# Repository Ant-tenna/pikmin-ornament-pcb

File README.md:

# Pikmin ornament

## What it is?
Is a christmas tree ornament PCB designed with the shape of a pikmin. The lights blink every few seconds being driven by a 555 timer
and powered by a 3v coin cell battery. I was inspired by those images of the yellow pikmin with the christmas leds! lovethem

## BOM

| Component | Value | Quantity |
|------|-------|----------|
| 555 timer | - | 1 |
| Coin cell battery holder | - | 1 |
| Capacitor | (10µF) | 1 |
| 5mm LED | - | 4 |
| Not polarized capacitor |(100nF) | 1 |
| Resistor | 470Ω | 4 |
| Resistor | 4.7kΩ | 1 |
| Resistor | 47kΩ | 1 |

## Schematic

## PCB

## 3D View

### Slack
@ant.tenn4

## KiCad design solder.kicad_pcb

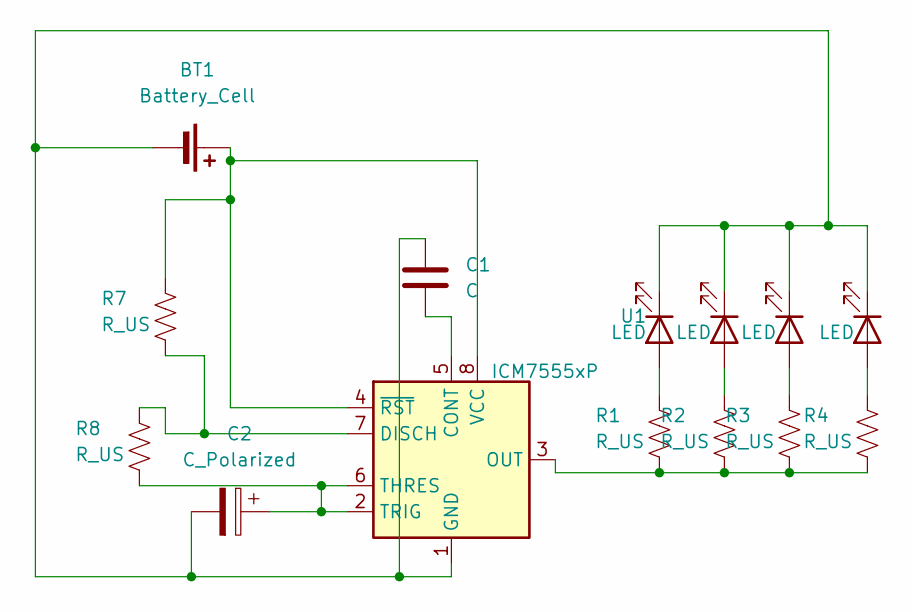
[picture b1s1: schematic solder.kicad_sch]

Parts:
BT1: Battery_Cell; BatteryHolder_Keystone_3034_1x20mm
C1: C; C_Disc_D7.5mm_W5.0mm_P5.00mm
C2: C_Polarized; CP_Radial_D8.0mm_P5.00mm
D1, D2, D3, D6: LED; LED_D5.0mm
R1, R2, R3, R4, R7, R8: R_US; R_Axial_DIN0207_L6.3mm_D2.5mm_P7.62mm_Horizontal
U1: ICM7555xP; DIP-8_W7.62mm

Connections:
GND: BT1.2 (-), C1.1, C2.2, D1.1 (K), D2.1 (K), D3.1 (K), D6.1 (K), U1.1 (GND)
unnamed: BT1.1 (+), R7.1, U1.4 (~RST), U1.8 (VCC)
unnamed: D1.2 (A), R2.1
unnamed: D2.2 (A), R3.1
unnamed: D3.2 (A), R4.1
unnamed: D6.2 (A), R1.1
unnamed: C1.2, U1.5 (CONT)
unnamed: R7.2, R8.1, U1.7 (DISCH)
unnamed: R1.2, R2.2, R3.2, R4.2, U1.3 (OUT)
unnamed: C2.1, R8.2, U1.2 (TRIG), U1.6 (THRES)

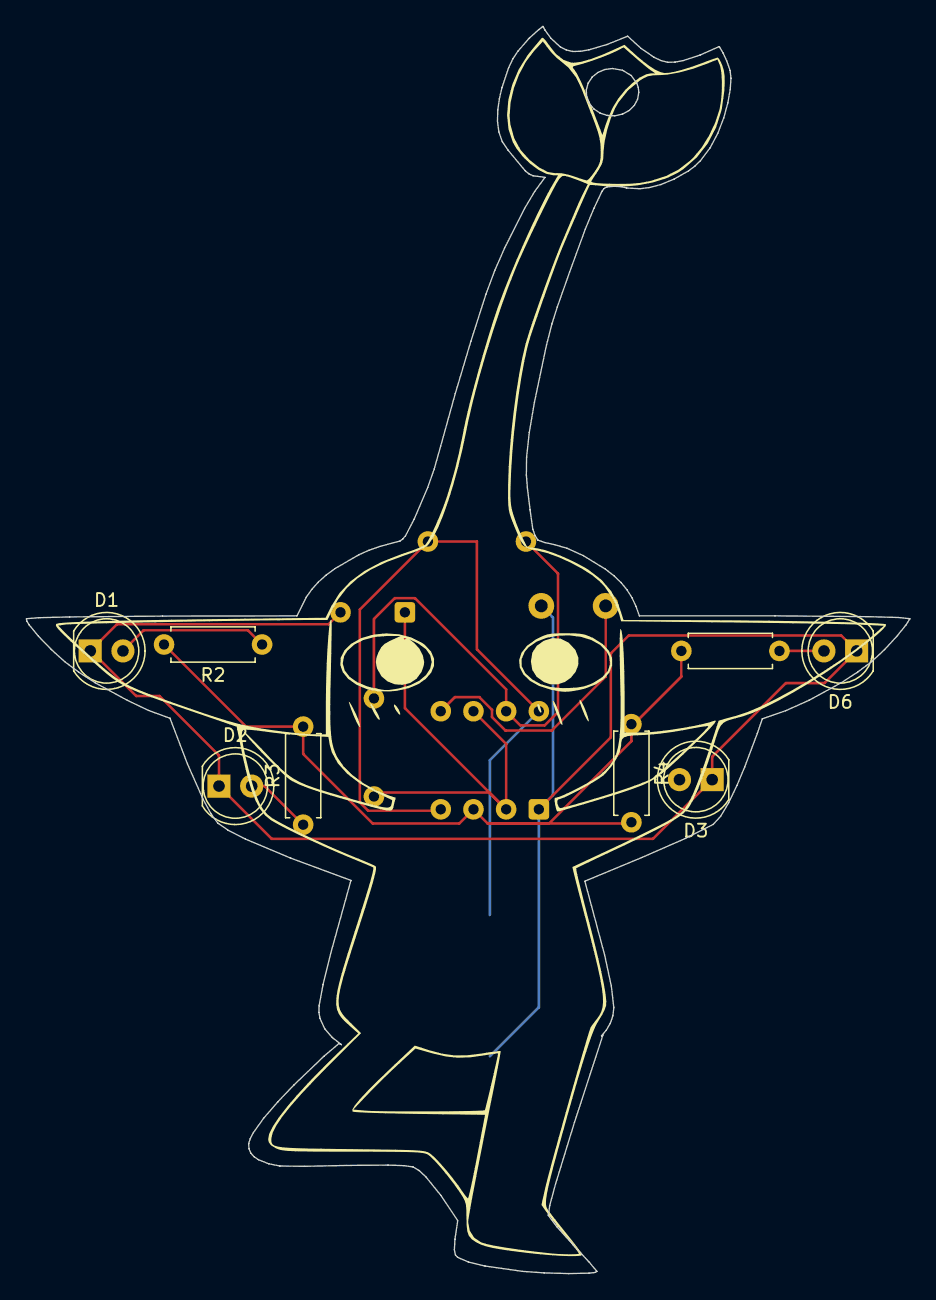
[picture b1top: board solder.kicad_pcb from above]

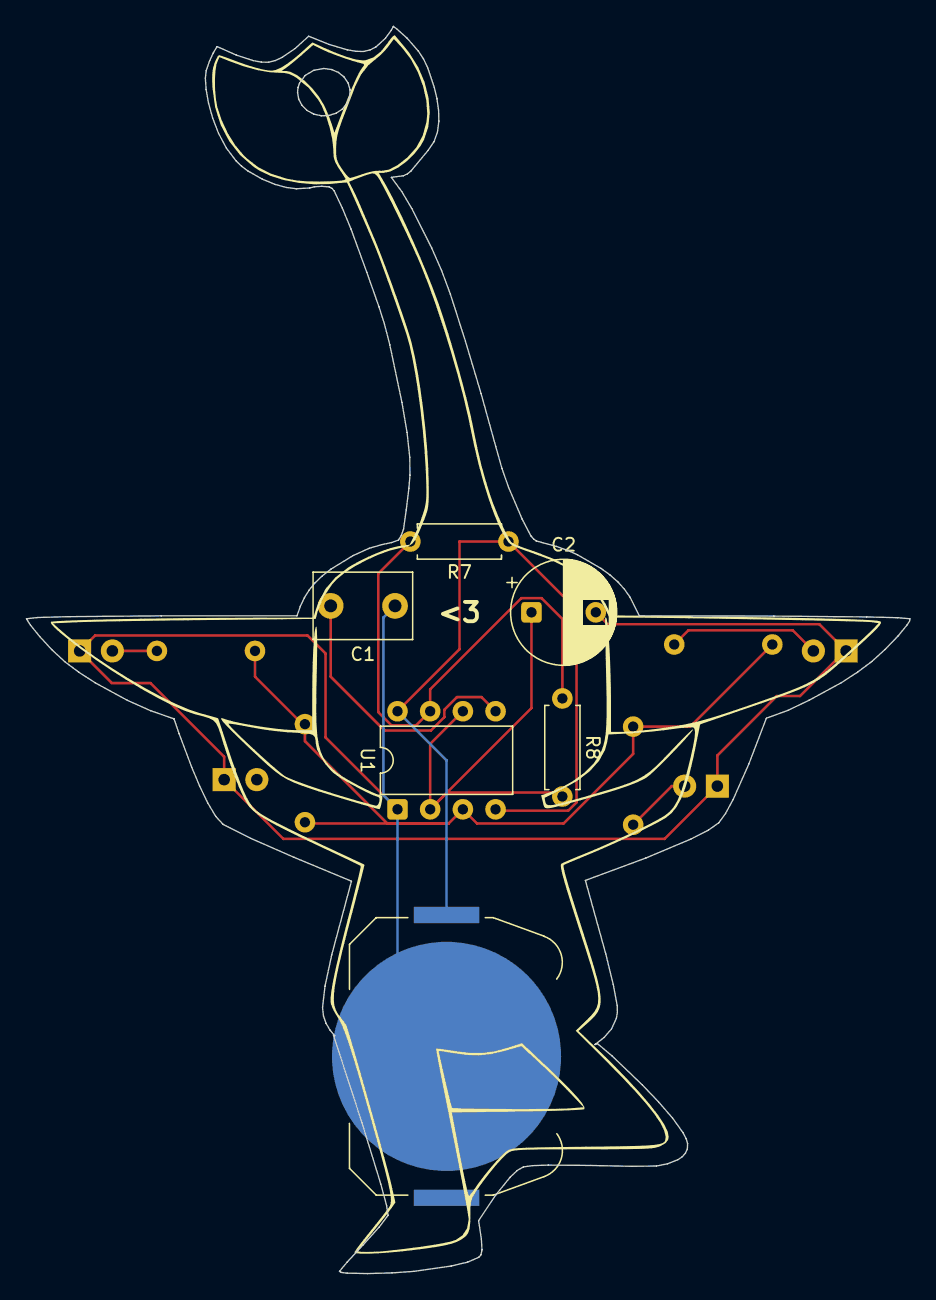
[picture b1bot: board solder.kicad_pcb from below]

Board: 2 copper layers, 68.6 x 96.9 mm, 16 parts (6 on the bottom side), 10 nets.

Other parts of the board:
<3: LOGO
pikumin: LOGO
